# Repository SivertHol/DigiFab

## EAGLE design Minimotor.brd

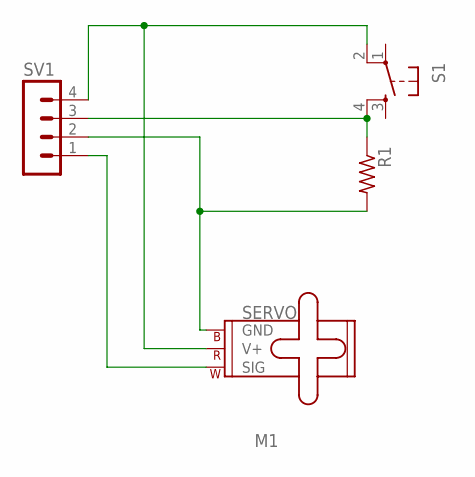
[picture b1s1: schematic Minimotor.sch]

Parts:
M1: SERVO; 1X03
R1: R-US_0204/7; 0204/7
S1: TAC_SWITCHPTH; TACTILE-PTH
SV1: MA04-1

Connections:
unnamed: R1.1, S1.4, SV1.3
unnamed: M1.3 (GND), R1.2, SV1.2
unnamed: M1.1 (SIG), SV1.1
unnamed: M1.2 (V+), S1.2, SV1.4

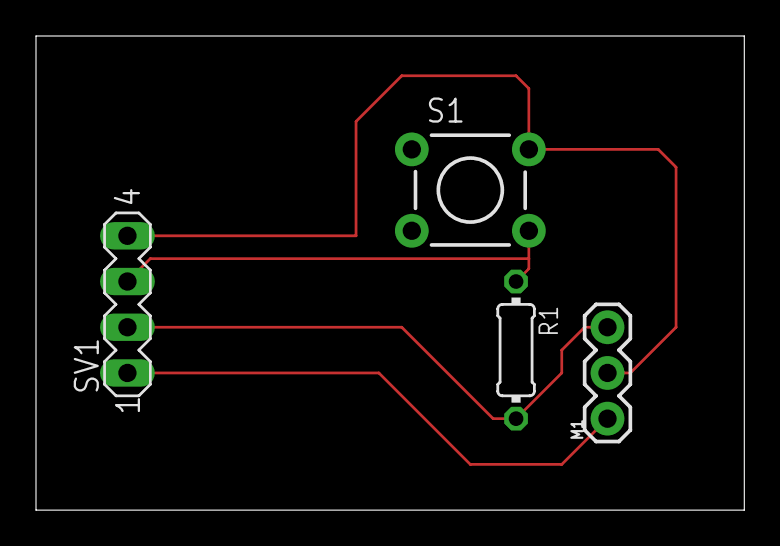
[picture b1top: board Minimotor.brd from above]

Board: 2 copper layers, 39.4 x 26.3 mm, 4 parts (0 on the bottom side), 4 nets.

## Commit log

2022-09-28 First Commit
    Alle sidene, kun forside som er ferdig
2022-11-27 Lagt til Bilder
2022-11-27 Lagt til 360 bilde av potta
2023-02-19 Elektronikk oblig
    Hele prosjektet, minus selve koden
2023-02-19 Lyskryss Kode
2023-03-26 PCB Design

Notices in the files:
parts and their libraries:
SparkFun-Electromechanical: Licensing: Creative Commons ShareAlike 4.0 International - https://creativecommons.org/licenses/by-sa/4.0
